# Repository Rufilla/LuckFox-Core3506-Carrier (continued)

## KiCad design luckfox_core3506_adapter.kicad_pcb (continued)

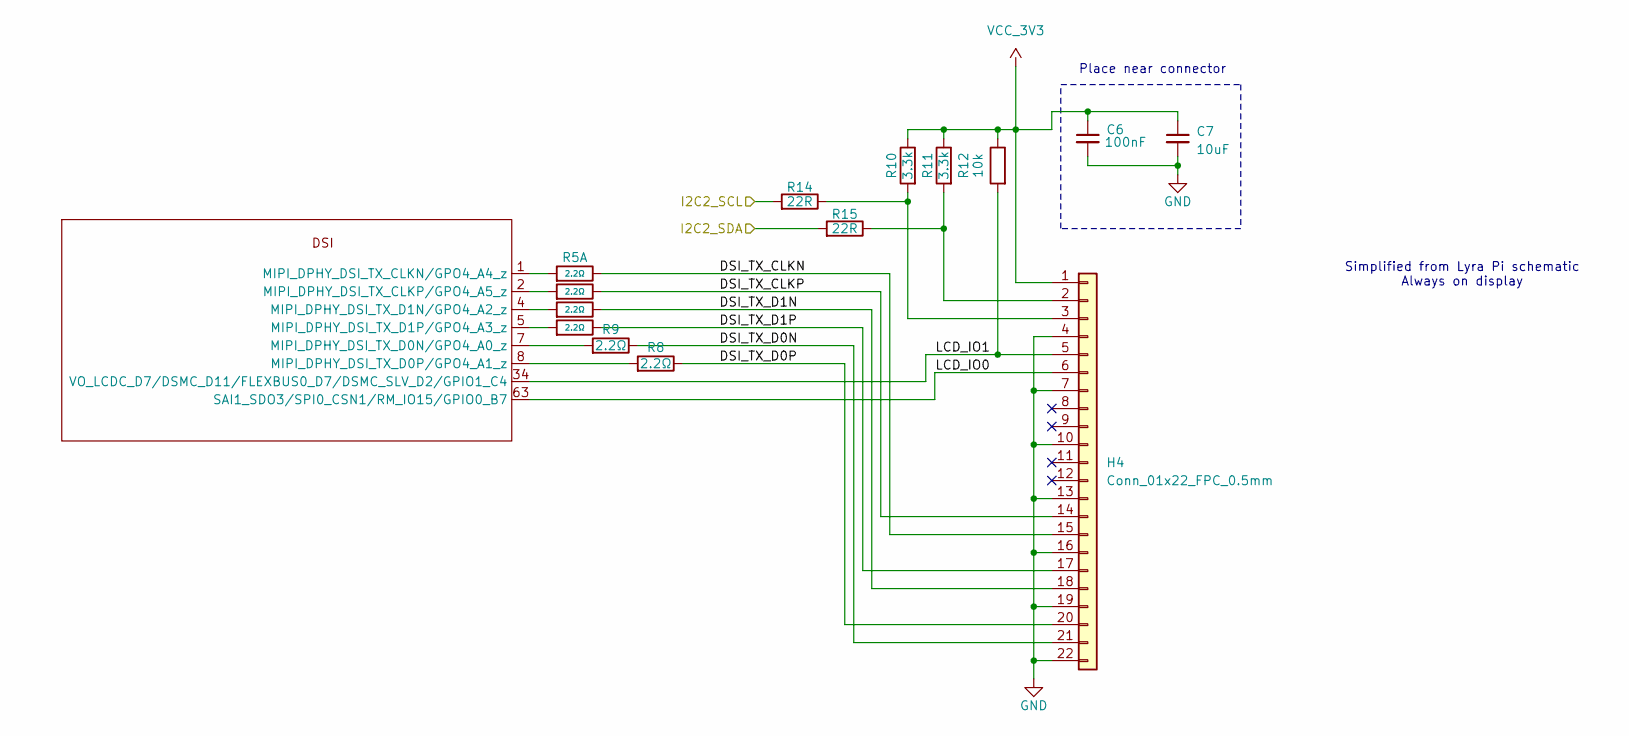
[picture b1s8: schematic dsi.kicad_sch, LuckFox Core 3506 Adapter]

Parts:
C6: 100nF; C_0603_1608Metric; Voltage 1kV; Tolerance 100%; LCSC C14663
C7: 10uF; C_0603_1608Metric; LCSC C19702
H4: Conn_01x22_FPC_0.5mm; FPC_1x22_P0.5mm_Horizontal_BottomContact; LCSC C262668
R5: 2.2Ω; R_0603x4; Tolerance ±5%; Part 4D03WGJ022JT5E; LCSC C12002
R8, R9: 2.2Ω; R_0603_1608Metric; LCSC C22939
R10, R11: 3.3k; R_0603_1608Metric; LCSC C22978
R12: 10k; R_0603_1608Metric; LCSC C25804
R14, R15: 22R; R_0603_1608Metric; LCSC C23345
U1: CORE3506_[32_32]_120P

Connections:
/DSI/DSI_TX_CLKN: H4.15, R5.5
/DSI/DSI_TX_CLKP: H4.14, R5.6
/DSI/DSI_TX_D0N: H4.21, R9.2
/DSI/DSI_TX_D0P: H4.20, R8.2
/DSI/DSI_TX_D1N: H4.18, R5.7
/DSI/DSI_TX_D1P: H4.17, R5.8
/DSI/I2C2_SCL: R14.1; also elsewhere on the board
/DSI/I2C2_SDA: R15.1; also elsewhere on the board
/DSI/LCD_IO0: H4.6, U1.63 (SAI1_SDO3/SPI0_CSN1/RM_IO15/GPIO0_B7)
/DSI/LCD_IO1: H4.5, R12.1, U1.34 (VO_LCDC_D7/DSMC_D11/FLEXBUS0_D7/DSMC_SL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)
GND: C6.2, C7.2, H4.4, H4.7, H4.10, H4.13, H4.16, H4.19, H4.22; also elsewhere on the board
unnamed: H4.2, R11.1, R15.2
unnamed: H4.3, R10.1, R14.2
unnamed: R5.4, U1.1 (MIPI_DPHY_DSI_TX_CLKN/GPO4_A4_z)
unnamed: R5.3, U1.2 (MIPI_DPHY_DSI_TX_CLKP/GPO4_A5_z)
unnamed: R9.1, U1.7 (MIPI_DPHY_DSI_TX_D0N/GPO4_A0_z)
unnamed: R8.1, U1.8 (MIPI_DPHY_DSI_TX_D0P/GPO4_A1_z)
unnamed: R5.2, U1.4 (MIPI_DPHY_DSI_TX_D1N/GPO4_A2_z)
unnamed: R5.1, U1.5 (MIPI_DPHY_DSI_TX_D1P/GPO4_A3_z)
VCC_3V3: C6.1, C7.1, H4.1, R10.2, R11.2, R12.2; also elsewhere on the board

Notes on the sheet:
Place near connector
Simplified from Lyra Pi schematic Always on display

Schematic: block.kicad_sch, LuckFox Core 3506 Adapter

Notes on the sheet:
RMII0 TX/RX MDIO/MDC
Booting: Recovery button released: 1. eMMC 2. SD Recovery button pressed at reset: Enumerate as USB device
NPOR_L SARADC_IN0 UART0_TX/RX
USB-C OTG1 (Host) 500mA Limit
Voltage Converter 5v to 3.3v LDO ME6217C33M5G
Power Flow: USB-C OTG0 VBUS → 5V Rail → SOM -> Ancillaries USB OTG1 powered from 5V rail via TPS2553 current limiter
USB-C Power & Flash
TF/SD Card SDMMC TF-110 Socket Card Detect
5v/ 1A
3.3v
VBUS Out
System Block Diagram
Boot & Debug MASKROM Button Reset Button UART Debug Header
Future Addition
GPIO Header 40 Pin
USB D+/D-
SDMMC CLK/CMD D0-D3
LuckFox Core3506 3 x Cortex A7 1 x Cortex M0 512MB DDR3L 8GB eMMC (Optional) 32mm x 32mm 120 castellated holes
Ethernet RMII0 HR911105A RJ45 + Magnetics
• USB-C OTG0: Device/Flash + Power Input • USB-C OTG1: Host (500mA protected) • RJ45 Ethernet (10/100 Mbps) • TF Card Socket (microSD) • UART Debug Header • Boot/Reset Buttons • Power & Status LEDs
VBUS Switch TPS2553 500mA Limit
USB D+/D- VBUSDET ID

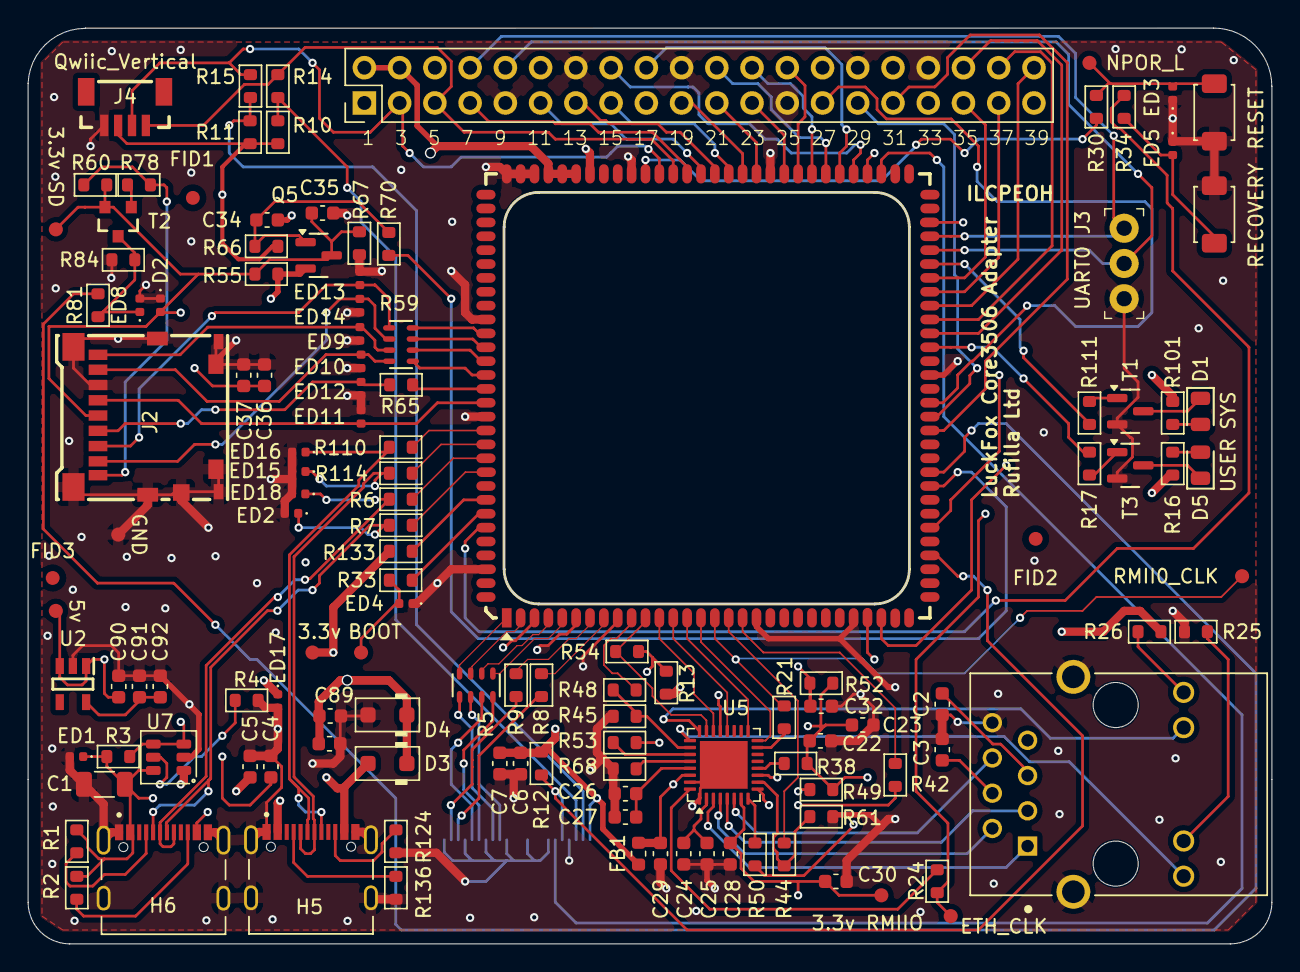
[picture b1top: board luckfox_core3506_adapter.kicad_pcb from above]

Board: 4 copper layers, 89.7 x 66.0 mm, 131 parts (1 on the bottom side), 132 nets.

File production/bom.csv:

Designator,Footprint,Quantity,Value,LCSC Part #
C1,1206,1,100uF,C15008
"C2, C23, C24, C26, C28, C29, C3, C32, C34, C35, C37, C4, C5, C6, C88",0603,15,100nF,C14663
"C22, C30, C36",0603,3,4.7uF,C19666
"C25, C27",0603,2,1uF,C15849
"C7, C89",0603,2,10uF,C19702
D1,D_0805,1,SYS,C2297
"D2, ED10, ED11, ED12, ED13, ED14, ED15, ED16, ED18, ED2, ED3, ED4, ED5, ED8, ED9",0402,15,ESD5341N,C20612964
D3,D_SOD-123F,1,MBR230SFT,C5377812
D4,D_SOD-123F,1,SMF5.0A,C19077498
D5,D_0805,1,USER,C2297
"ED1, ED17",0402,2,ESD5451N,C2936977
FB1,0603,1,330Ω@100MHz,C88989
H4,FPC_1x22_P0.5mm_Horizontal_BottomContact,1,Conn_01x22_FPC_0.5mm,C262668
"H5, H6",TYPE-C_16PIN_2MD_073,2,TYPE-C_16PIN_2MD__073_,C2765186
J1,HANRUN_HR911105A,1,HR911105A,C12074
J2,TF-SMD_TF-110,1,TF-110,C266613
KEY1,SW_TS-1088-AR02016,1,RESET,C720477
KEY2,SW_TS-1088-AR02016,1,RECOVERY,C720477
Q5,Q_SOT-23,1,SI2301CDS-T1-GE3,C10487
"R1, R2, R4",0603,3,56k,C23206
"R10, R11",0603,2,3.3k,C22978
"R101, R16",0603,2,470R,C23179
"R110, R114, R14, R15, R42, R44, R48, R6, R65, R7",0603,10,22R,C23345
"R111, R17, R78, R81",0603,4,1k,C21190
"R12, R133, R60, R67, R70, R84",0603,6,10k,C25804
"R124, R136",0603,2,5.1k,C23186
"R13, R21, R24",0603,3,0R,C21189
"R25, R26",0603,2,510R,C23193
"R3, R66",0603,2,100k,C25803
"R30, R33, R34",0603,3,100R,C22775
"R38, R45, R49, R50, R61, R68",0603,6,4.7K,C23162
R5,R_0603x4,1,2.2Ω,C12002
R54,0603,1,1.8k,C4177
R59,R_0603x4,1,22R,C12008
"R8, R9",0603,2,2.2Ω,C22939
"T1, T3",Q_SOT-23,2,SS8050 200-350,C2150
T2,SOT23-3,1,MMBT3906,C2149
U5,QFN-32-1EP_5x5mm_P0.5mm_EP3.45x3.45mm,1,CH182H2,C41427683
U7,SOT-23-6,1,TPS2553DBVR,C55266
